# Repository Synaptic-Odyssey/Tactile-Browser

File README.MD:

ABSTRACT:

This project aims to develop a tactile web browsing interface for blind and visually impaired users. Current assistive technology, such as screen readers, forces linear navigation through web pages, preventing users from perceiving spatial layout and efficiently locating interactive elements. The proposed system consists of a 17×11 grid of uniform keycaps (with keyswitches that double as input) that move along the Z-axis using bistable solenoids. Each grouping of blocks represents a distinct webpage element (e.g., headers, links, buttons). When a block is pressed down, the system provides audio feedback, reading the element’s content; prolonged touch can select the element and allow the user to interact with it. By mapping webpage structures into a physical tactile representation, users can explore content spatially and intuitively. Estimated cost for the prototype is ~$800. The project timeline spans two quarters, starting implementing webpage-to-grid mapping, then with the creation of a single 2x5 module, before integrating the entire design.

Detailed Presentation: https://docs.google.com/presentation/d/1p2b0jzcivFLc2I2OcCCj18AWDXcFEL55aIJLbLz9RJQ/edit?slide=id.g39ac1d9ecba_0_35#slide=id.g39ac1d9ecba_0_35

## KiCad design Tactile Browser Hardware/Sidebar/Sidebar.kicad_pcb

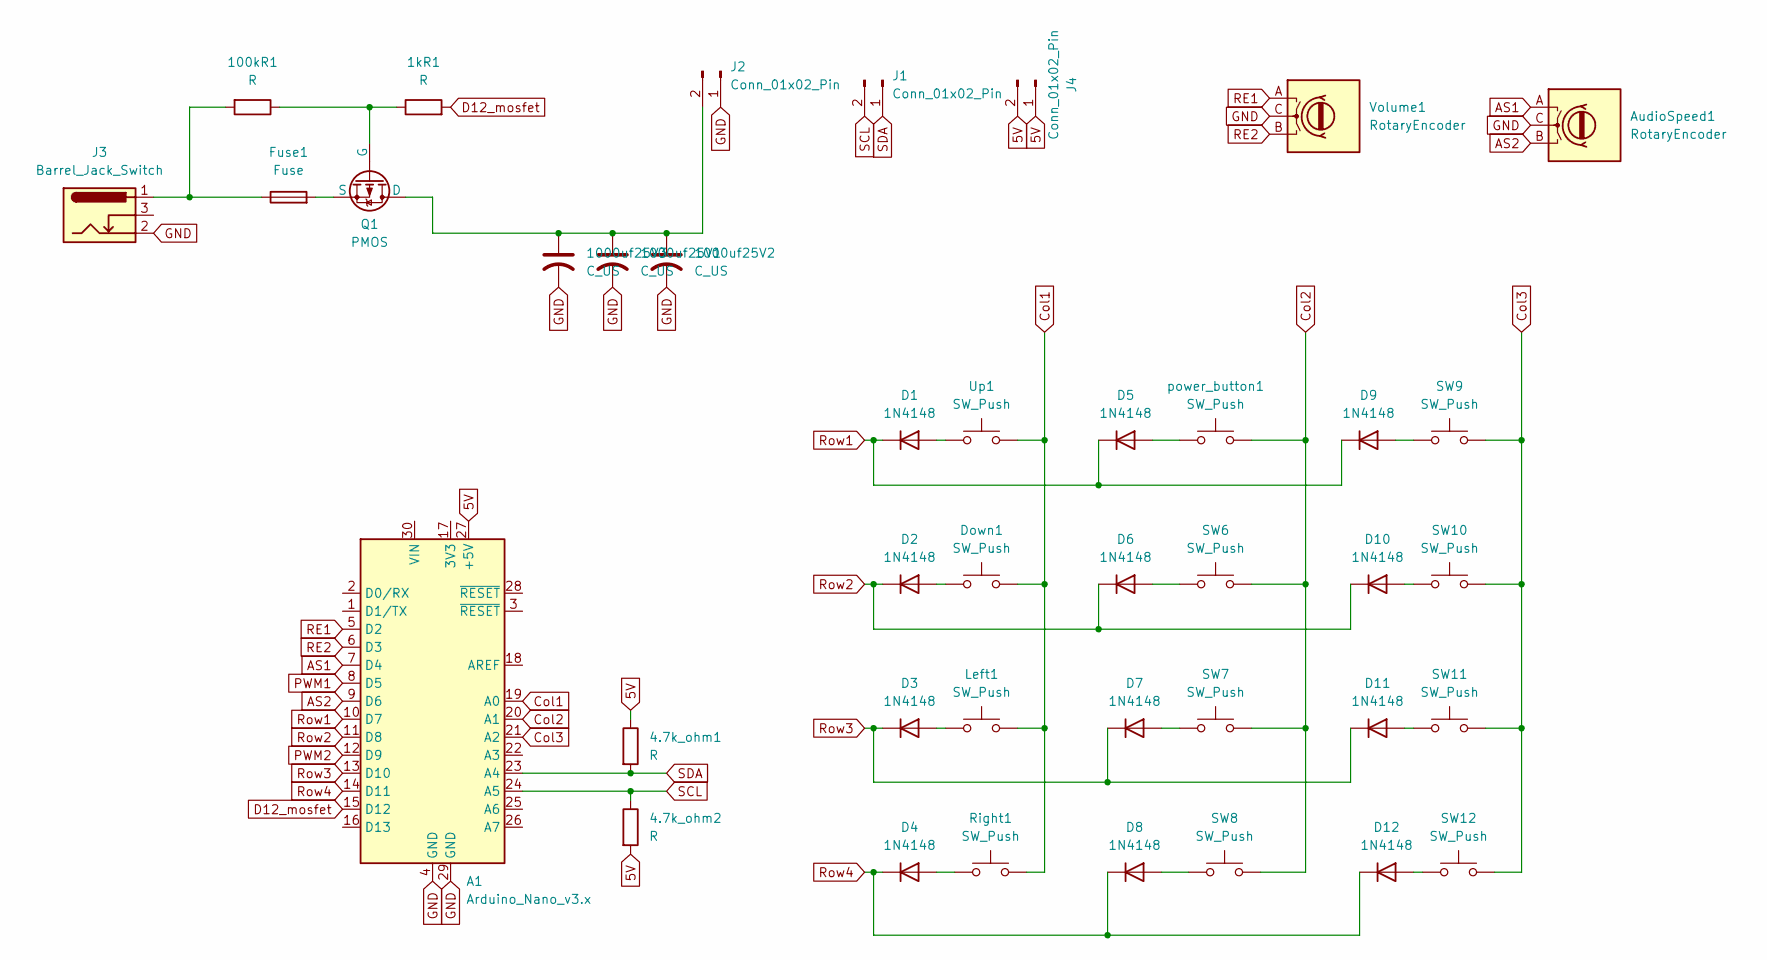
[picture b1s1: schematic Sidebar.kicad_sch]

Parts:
1kR1, 100kR1: R; R_0805_2012Metric
4.7k_ohm1, 4.7k_ohm2: R; R_0402_1005Metric
1000uf25V1, 1000uf25V2, 1000uf25V3: C_US; CP_Elec_10x12.5
A1: Arduino_Nano_v3.x; Arduino_Nano
AudioSpeed1: RotaryEncoder; RotaryEncoder_Alps_EC11E-Switch_Vertical_H20mm
D1, D2, D3, D4, D5, D6, D7, D8, D9, D10, D11, D12: 1N4148; D_SOD-123
Down1: SW_Push; SW_SPST_EVQQ2
Fuse1: Fuse; FUSE_3560
J1, J4: Conn_01x02_Pin; JST_PH_B2B-PH-SM4-TB_1x02-1MP_P2.00mm_Vertical
J2: Conn_01x02_Pin; ScrewTerminal_Vertical_1935310
J3: Barrel_Jack_Switch; BarrelJack_CUI_PJ-063AH_Horizontal
Left1: SW_Push; SW_SPST_EVQQ2
Q1: PMOS; TO-252-3_TabPin2
Right1: SW_Push; SW_SPST_EVQQ2
SW6, SW7, SW8, SW9, SW10, SW11, SW12: SW_Push; SW_SPST_EVQQ2
Up1: SW_Push; SW_SPST_EVQQ2
Volume1: RotaryEncoder; RotaryEncoder_Alps_EC11E-Switch_Vertical_H20mm
power_button1: SW_Push; SW_SPST_EVQQ2

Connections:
5V: 4.7k_ohm1.1, 4.7k_ohm2.2, A1.27 (+5V), J4.1, J4.2
AS1: A1.7 (D4), AudioSpeed1.A
AS2: A1.9 (D6), AudioSpeed1.B
Col1: A1.19 (A0), Down1.2, Left1.2, Right1.2, Up1.2
Col2: A1.20 (A1), SW6.2, SW7.2, SW8.2, power_button1.2
Col3: A1.21 (A2), SW9.2, SW10.2, SW11.2, SW12.2
D12_mosfet: 1kR1.2, A1.15 (D12); also elsewhere on the board
GND: 1000uf25V1.2, 1000uf25V2.2, 1000uf25V3.2, A1.4 (GND), A1.29 (GND), AudioSpeed1.C, J2.1, J3.2, Volume1.C
unnamed 8: 100kR1.2, Fuse1.1, J3.1; also elsewhere on the board
unnamed: D1.2 (A), Up1.1
unnamed: D2.2 (A), Down1.1
unnamed: D3.2 (A), Left1.1
unnamed: D4.2 (A), Right1.1
unnamed: D5.2 (A), power_button1.1
unnamed: D6.2 (A), SW6.1
unnamed: D7.2 (A), SW7.1
unnamed: D8.2 (A), SW8.1
unnamed: D9.2 (A), SW9.1
unnamed: D10.2 (A), SW10.1
unnamed: D11.2 (A), SW11.1
unnamed: D12.2 (A), SW12.1
unnamed: 1000uf25V1.1, 1000uf25V2.1, 1000uf25V3.1, J2.2, Q1.1 (D)
unnamed 22: 1kR1.1, 100kR1.1, Q1.2 (G); also elsewhere on the board
unnamed: Fuse1.2, Q1.3 (S)
PWM1: A1.8 (D5)
PWM2: A1.12 (D9)
RE1: A1.5 (D2), Volume1.A
RE2: A1.6 (D3), Volume1.B
Row1: A1.10 (D7), D1.1 (K), D5.1 (K), D9.1 (K)
Row2: A1.11 (D8), D2.1 (K), D6.1 (K), D10.1 (K)
Row3: A1.13 (D10), D3.1 (K), D7.1 (K), D11.1 (K)
Row4: A1.14 (D11), D4.1 (K), D8.1 (K), D12.1 (K)
SCL: 4.7k_ohm2.1, A1.24 (A5), J1.2
SDA: 4.7k_ohm1.2, A1.23 (A4), J1.1

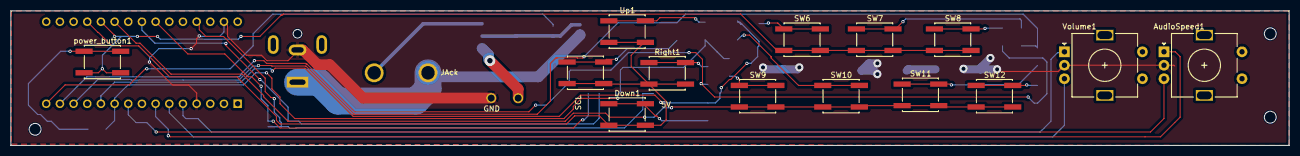
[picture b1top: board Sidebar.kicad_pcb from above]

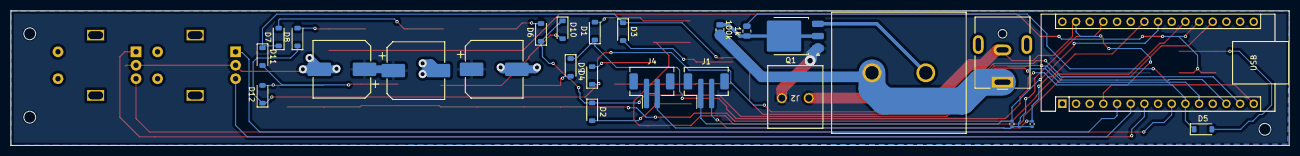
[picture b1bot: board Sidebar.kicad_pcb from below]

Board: 2 copper layers, 237.5 x 25.0 mm, 40 parts (26 on the bottom side), 32 nets.

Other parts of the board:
1k, 100k: R; R_0805_2012Metric

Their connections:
D12_mosfet: 1k.2; also elsewhere on the board
unnamed 8: 100k.2; also elsewhere on the board
unnamed 22: 1k.1, 100k.1; also elsewhere on the board

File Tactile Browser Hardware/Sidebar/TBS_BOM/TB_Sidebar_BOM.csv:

Designator,Comment,Footprint,LCSC Part #
Volume1,RotaryEncoder,RotaryEncoder_Alps_EC11E-Switch_Vertical_H20mm,HAND_SOLDER
AudioSpeed1,RotaryEncoder,RotaryEncoder_Alps_EC11E-Switch_Vertical_H20mm,HAND_SOLDER
power_button1,SW_Push,SW_SPST_EVQQ2,C2976606
Right1,SW_Push,SW_SPST_EVQQ2,C2976606
Down1,SW_Push,SW_SPST_EVQQ2,C2976606
SW10,SW_Push,SW_SPST_EVQQ2,C2976606
Left1,SW_Push,SW_SPST_EVQQ2,C2976606
SW8,SW_Push,SW_SPST_EVQQ2,C2976606
SW6,SW_Push,SW_SPST_EVQQ2,C2976606
Up1,SW_Push,SW_SPST_EVQQ2,C2976606
SW12,SW_Push,SW_SPST_EVQQ2,C2976606
SW11,SW_Push,SW_SPST_EVQQ2,C2976606
SW7,SW_Push,SW_SPST_EVQQ2,C2976606
SW9,SW_Push,SW_SPST_EVQQ2,C2976606
1kR1,R,R_0805_2012Metric,C727989
100kR1,R,R_0805_2012Metric,C161786
A1,Arduino_Nano_v3.x,Arduino_Nano,HAND_SOLDER
1000uf25V2,C_US,CP_Elec_10x12.5,C49256851
1000uf25V3,C_US,CP_Elec_10x12.5,C49256851
1000uf25V1,C_US,CP_Elec_10x12.5,C49256851
D8,1N4148,D_SOD-123,C917030
D9,1N4148,D_SOD-123,C917030
D10,1N4148,D_SOD-123,C917030
D5,1N4148,D_SOD-123,C917030
D6,1N4148,D_SOD-123,C917030
D12,1N4148,D_SOD-123,C917030
D11,1N4148,D_SOD-123,C917030
D3,1N4148,D_SOD-123,C917030
D2,1N4148,D_SOD-123,C917030
D1,1N4148,D_SOD-123,C917030
D4,1N4148,D_SOD-123,C917030
D7,1N4148,D_SOD-123,C917030
Q1,PMOS,TO-252-3_TabPin2,HAND_SOLDER
Fuse1,Fuse,FUSE_3560,HAND_SOLDER
J2,Conn_01x02_Pin,ScrewTerminal_Vertical_1935310,HAND_SOLDER
J4,Conn_01x02_Pin,JST_PH_B2B-PH-SM4-TB_1x02-1MP_P2.00mm_Vertical,C160352
J1,Conn_01x02_Pin,JST_PH_B2B-PH-SM4-TB_1x02-1MP_P2.00mm_Vertical,C160352
4.7k_ohm2,R,R_0402_1005Metric,C105871
4.7k_ohm1,R,R_0402_1005Metric,C105871
J3,Barrel_Jack_Switch,BarrelJack_CUI_PJ-063AH_Horizontal,HAND_SOLDER

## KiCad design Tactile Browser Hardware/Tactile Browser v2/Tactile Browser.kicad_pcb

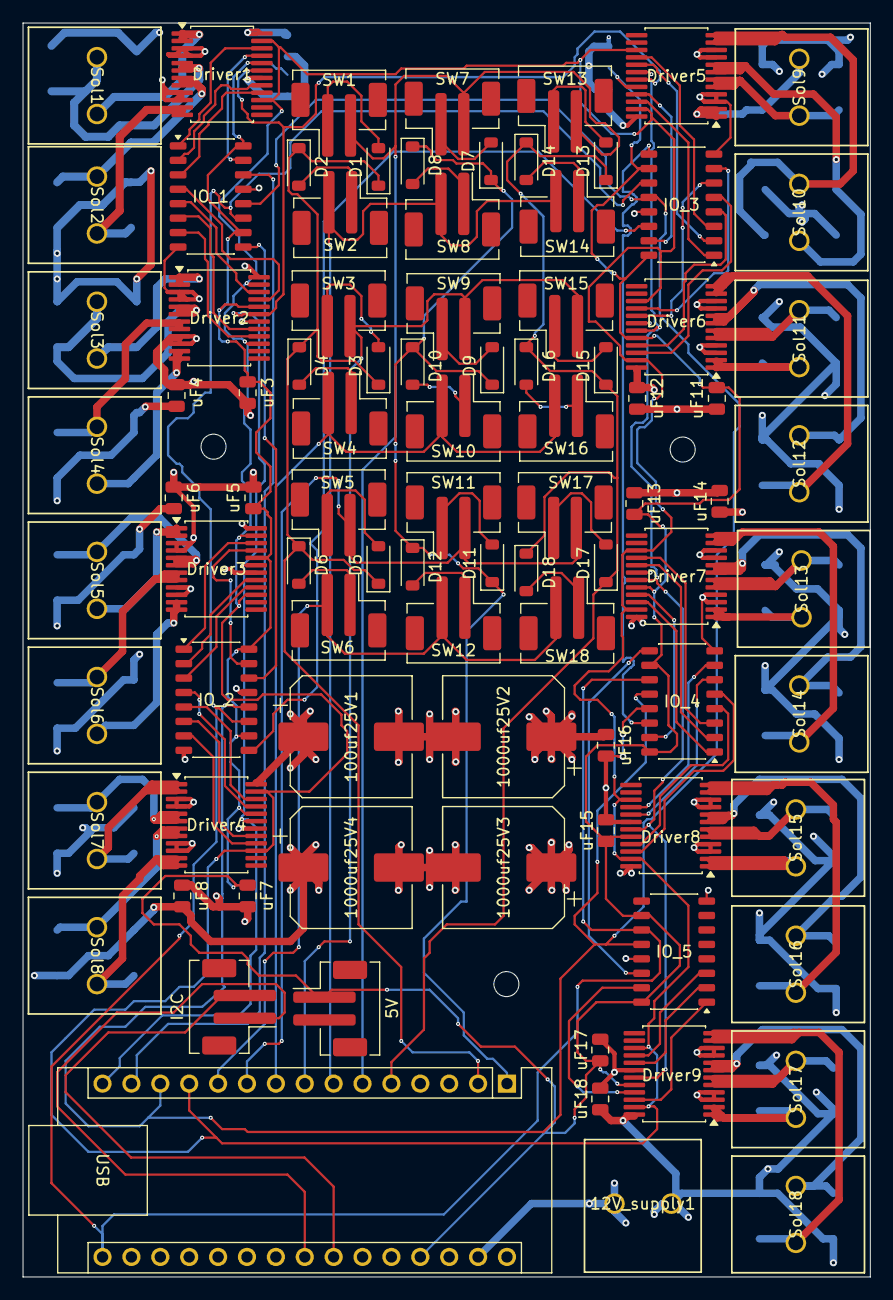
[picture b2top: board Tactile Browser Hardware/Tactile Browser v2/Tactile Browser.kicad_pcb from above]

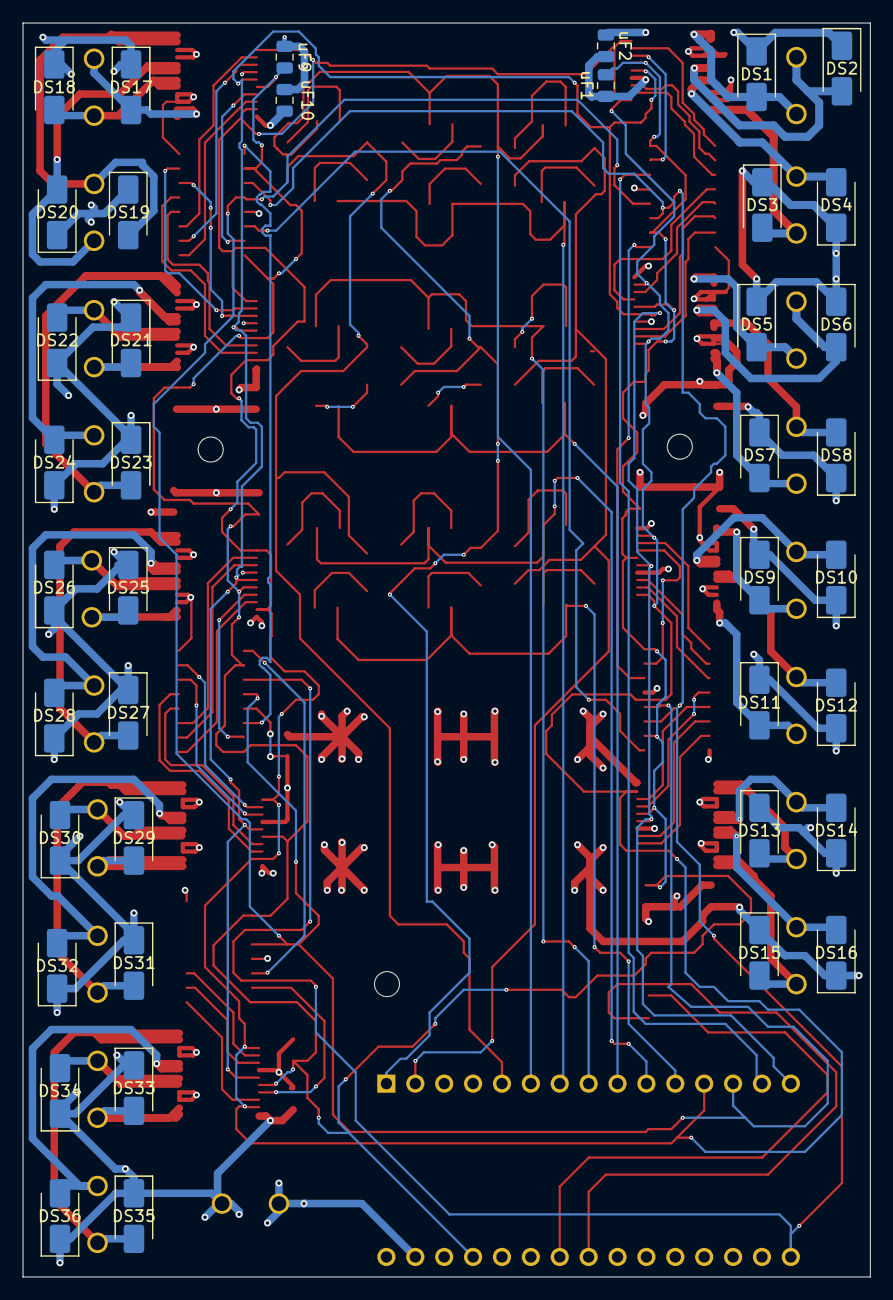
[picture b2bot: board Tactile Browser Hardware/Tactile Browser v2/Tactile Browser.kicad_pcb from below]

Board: 4 copper layers, 74.5 x 110.2 mm, 130 parts (40 on the bottom side), 113 nets.

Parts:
5V: Conn_01x01_Pin; JST_PH_B2B-PH-SM4-TB_1x02-1MP_P2.00mm_Vertical
12V_supply1: Conn_01x02_Pin; ScrewTerminal_Vertical_1935310
100uf25V1, 1000uf25V2, 1000uf25V3, 1000uf25V4: C_Polarized; CP_Elec_10x12.5
A1: Arduino_Nano_v3.x; Arduino_Nano
D1, D2, D3, D4, D5, D6, D7, D8, D9, D10, D11, D12, D13, D14, D15, D16, D17, D18: 1N4148; D_SOD-123
DS1, DS2, DS3, DS4, DS5, DS6, DS7, DS8, DS9, DS10, DS11, DS12, DS13, DS14, DS15, DS16, DS17, DS18, DS19, DS20, DS21, DS22, DS23, DS24, DS25, DS26, DS27, DS28, DS29, DS30, DS31, DS32, DS33, DS34, DS35, DS36: D_Schottky; D_SMA
Driver1, Driver2, Driver3, Driver4, Driver5, Driver6, Driver7, Driver8, Driver9: TB6612FNG; SSOP-24_5.3x8.2mm_P0.65mm
I2C: Conn_01x02_Pin; JST_PH_B2B-PH-SM4-TB_1x02-1MP_P2.00mm_Vertical
IO_1, IO_2, IO_3, IO_4, IO_5: 74HC595; JEITA_SOIC-16_3.9x9.9mm_P1.27mm
SW1, SW2, SW3, SW4, SW5, SW6, SW7, SW8, SW9, SW10, SW11, SW12, SW13, SW14, SW15, SW16, SW17, SW18: SW_Push; JST_PH_B2B-PH-SM4-TB_1x02-1MP_P2.00mm_Vertical
Sol1, Sol2, Sol3, Sol4, Sol5, Sol6, Sol7, Sol8, Sol9, Sol10, Sol11, Sol12, Sol13, Sol14, Sol15, Sol16, Sol17, Sol18: Conn_01x02_Pin; ScrewTerminal_Vertical_1935310
uF1, uF2, uF3, uF4, uF5, uF6, uF7, uF8, uF9, uF10, uF11, uF12, uF13, uF14, uF15, uF16, uF17, uF18: C; C_0805_2012Metric

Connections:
5V: 5V.1, A1.27 (+5V), Driver1.20 (VCC), Driver2.20 (VCC), Driver3.20 (VCC), Driver4.20 (VCC), Driver5.20 (VCC), Driver6.20 (VCC), Driver7.20 (VCC), Driver8.20 (VCC), Driver9.20 (VCC), IO_1.10 (~SRCLR), IO_1.16 (VCC), IO_2.10 (~SRCLR), IO_2.16 (VCC), IO_3.10 (~SRCLR), IO_3.16 (VCC), IO_4.10 (~SRCLR), IO_4.16 (VCC), IO_5.10 (~SRCLR), IO_5.16 (VCC), uF1.2, uF3.2, uF5.2, uF7.1, uF9.1, uF11.1, uF13.1, uF15.1, uF17.1
12V: 12V_supply1.2, 100uf25V1.1, 1000uf25V2.1, 1000uf25V3.1, 1000uf25V4.1, DS1.1 (K), DS2.1 (K), DS3.1 (K), DS4.1 (K), DS5.1 (K), DS6.1 (K), DS7.1 (K), DS8.1 (K), DS9.1 (K), DS10.1 (K), DS11.1 (K), DS12.1 (K), DS13.1 (K), DS14.1 (K), DS15.1 (K), DS16.1 (K), DS17.1 (K), DS18.1 (K), DS19.1 (K), DS20.1 (K), DS21.1 (K), DS22.1 (K), DS23.1 (K), DS24.1 (K), DS25.1 (K), DS26.1 (K), DS27.1 (K), DS28.1 (K), DS29.1 (K), DS30.1 (K), DS31.1 (K), DS32.1 (K), DS33.1 (K), DS34.1 (K), DS35.1 (K), DS36.1 (K), Driver1.24 (VM1), Driver2.24 (VM3), Driver3.24 (VM1), Driver4.24 (VM1), Driver5.24 (VM3), Driver6.24 (VM1), Driver7.24 (VM3), Driver8.24 (VM3), Driver9.24 (VM3), uF2.1, uF4.1, uF6.1, uF8.1, uF10.1, uF12.1, uF14.1, uF16.1, uF18.1
CLOCK: A1.16 (D13), IO_1.11 (SRCLK), IO_2.11 (SRCLK), IO_3.11 (SRCLK), IO_4.11 (SRCLK), IO_5.11 (SRCLK)
Col1: A1.2 (D0/RX), D1.1 (K), D2.1 (K), D3.1 (K), D4.1 (K), D5.1 (K), D6.1 (K)
Col2: A1.1 (D1/TX), D7.1 (K), D8.1 (K), D9.1 (K), D10.1 (K), D11.1 (K), D12.1 (K)
Col3: A1.5 (D2), D13.1 (K), D14.1 (K), D15.1 (K), D16.1 (K), D17.1 (K), D18.1 (K)
DATA: A1.14 (D11), IO_1.14 (SER)
GND: 12V_supply1.1, 100uf25V1.2, 1000uf25V2.2, 1000uf25V3.2, 1000uf25V4.2, A1.4 (GND), A1.29 (GND), Driver1.3 (PGND1), Driver1.4 (PGND1), Driver1.9 (PGND2), Driver1.10 (PGND2), Driver1.18 (GND), Driver2.3 (PGND1), Driver2.4 (PGND1), Driver2.9 (PGND2), Driver2.10 (PGND2), Driver2.18 (GND), Driver3.3 (PGND1), Driver3.4 (PGND1), Driver3.9 (PGND2), Driver3.10 (PGND2), Driver3.18 (GND), Driver4.3 (PGND1), Driver4.4 (PGND1), Driver4.9 (PGND2), Driver4.10 (PGND2), Driver4.18 (GND), Driver5.3 (PGND1), Driver5.4 (PGND1), Driver5.9 (PGND2), Driver5.10 (PGND2), Driver5.18 (GND), Driver6.3 (PGND1), Driver6.4 (PGND1), Driver6.9 (PGND2), Driver6.10 (PGND2), Driver6.18 (GND), Driver7.3 (PGND1), Driver7.4 (PGND1), Driver7.9 (PGND2), Driver7.10 (PGND2), Driver7.18 (GND), Driver8.3 (PGND1), Driver8.4 (PGND1), Driver8.9 (PGND2), Driver8.10 (PGND2), Driver8.18 (GND), Driver9.3 (PGND1), Driver9.4 (PGND1), Driver9.9 (PGND2), Driver9.10 (PGND2), Driver9.18 (GND), IO_1.8 (GND), IO_1.13 (~OE), IO_2.8 (GND), IO_2.13 (~OE), IO_3.8 (GND), IO_3.13 (~OE), IO_4.8 (GND), IO_4.13 (~OE), IO_5.8 (GND), IO_5.13 (~OE), uF1.1, uF2.2, uF3.1, uF4.2, uF5.1, uF6.2, uF7.2, uF8.2, uF9.2, uF10.2, uF11.2, uF12.2, uF13.2, uF14.2, uF15.2, uF16.2, uF17.2, uF18.2
LATCH: A1.13 (D10), IO_1.12 (RCLK), IO_2.12 (RCLK), IO_3.12 (RCLK), IO_4.12 (RCLK), IO_5.12 (RCLK)
unnamed: D1.2 (A), SW1.1
unnamed: D2.2 (A), SW2.1
unnamed: D3.2 (A), SW3.1
unnamed: D4.2 (A), SW4.1
unnamed: D5.2 (A), SW5.1
unnamed: D6.2 (A), SW6.1
unnamed: D7.2 (A), SW7.1
unnamed: D8.2 (A), SW8.1
unnamed: D9.2 (A), SW9.1
unnamed: D10.2 (A), SW10.1
unnamed: D11.2 (A), SW11.1
unnamed: D12.2 (A), SW12.1
unnamed: D13.2 (A), SW13.1
unnamed: D14.2 (A), SW14.1
unnamed: D15.2 (A), SW15.1
unnamed: D16.2 (A), SW16.1
unnamed: D17.2 (A), SW17.1
unnamed: D18.2 (A), SW18.1
Overflow1: IO_1.9 (QH'), IO_2.14 (SER)
Overflow2: IO_2.9 (QH'), IO_3.14 (SER)
Overflow3: IO_3.9 (QH'), IO_4.14 (SER)
Overflow4: IO_4.9 (QH'), IO_5.14 (SER)
PWM: A1.12 (D9), Driver1.15 (PWMB), Driver1.23 (PWMA), Driver2.15 (PWMB), Driver2.23 (PWMA), Driver3.15 (PWMB), Driver3.23 (PWMA), Driver4.15 (PWMB), Driver4.23 (PWMA), Driver5.15 (PWMB), Driver5.23 (PWMA), Driver6.15 (PWMB), Driver6.23 (PWMA), Driver7.15 (PWMB), Driver7.23 (PWMA), Driver8.15 (PWMB), Driver8.23 (PWMA), Driver9.15 (PWMB), Driver9.23 (PWMA)
Row1: A1.6 (D3), SW1.2, SW7.2, SW13.2
Row2: A1.7 (D4), SW2.2, SW8.2, SW14.2
Row3: A1.8 (D5), SW3.2, SW9.2, SW15.2
Row4: A1.9 (D6), SW4.2, SW10.2, SW16.2
Row5: A1.10 (D7), SW5.2, SW11.2, SW17.2
Row6: A1.11 (D8), SW6.2, SW12.2, SW18.2
S1_in1: Driver1.21 (AIN1), IO_1.15 (QA)
S1_in2: Driver1.22 (AIN2), IO_1.1 (QB)
S1_out1: DS1.2 (A), Driver1.1 (AO1), Driver1.2 (AO1), Sol1.2
S1_out2: DS2.2 (A), Driver1.5 (AO2), Driver1.6 (AO2), Sol1.1
S2_in1: Driver1.17 (BIN1), IO_1.2 (QC)
S2_in2: Driver1.16 (BIN2), IO_1.3 (QD)
S2_out1: DS3.2 (A), Driver1.11 (BO1), Driver1.12 (BO1), Sol2.2
S2_out2: DS4.2 (A), Driver1.7 (BO2), Driver1.8 (BO2), Sol2.1
S3_in1: Driver2.21 (AIN1), IO_1.4 (QE)
S3_in2: Driver2.22 (AIN2), IO_1.5 (QF)
S3_out1: DS5.2 (A), Driver2.1 (AO1), Driver2.2 (AO1), Sol3.2
S3_out2: DS6.2 (A), Driver2.5 (AO2), Driver2.6 (AO2), Sol3.1
S4_in1: Driver2.17 (BIN1), IO_1.6 (QG)
S4_in2: Driver2.16 (BIN2), IO_1.7 (QH)
S4_out1: DS7.2 (A), Driver2.11 (BO1), Driver2.12 (BO1), Sol4.2
S4_out2: DS8.2 (A), Driver2.7 (BO2), Driver2.8 (BO2), Sol4.1
S5_in1: Driver3.21 (AIN1), IO_2.15 (QA)
S5_in2: Driver3.22 (AIN2), IO_2.1 (QB)
S5_out1: DS9.2 (A), Driver3.1 (AO1), Driver3.2 (AO1), Sol5.2
S5_out2: DS10.2 (A), Driver3.5 (AO2), Driver3.6 (AO2), Sol5.1
S6_in1: Driver3.17 (BIN1), IO_2.2 (QC)
S6_in2: Driver3.16 (BIN2), IO_2.3 (QD)
S6_out1: DS11.2 (A), Driver3.11 (BO1), Driver3.12 (BO1), Sol6.2
S6_out2: DS12.2 (A), Driver3.7 (BO2), Driver3.8 (BO2), Sol6.1
S7_in1: Driver4.21 (AIN1), IO_2.4 (QE)
S7_in2: Driver4.22 (AIN2), IO_2.5 (QF)
S7_out1: DS13.2 (A), Driver4.1 (AO1), Driver4.2 (AO1), Sol7.2
S7_out2: DS14.2 (A), Driver4.5 (AO2), Driver4.6 (AO2), Sol7.1
S8_in1: Driver4.17 (BIN1), IO_2.6 (QG)
S8_in2: Driver4.16 (BIN2), IO_2.7 (QH)
S8_out1: DS15.2 (A), Driver4.11 (BO1), Driver4.12 (BO1), Sol8.2
S8_out2: DS16.2 (A), Driver4.7 (BO2), Driver4.8 (BO2), Sol8.1
S9_in1: Driver5.21 (AIN1), IO_3.15 (QA)
S9_in2: Driver5.22 (AIN2), IO_3.1 (QB)
S9_out1: DS17.2 (A), Driver5.1 (AO1), Driver5.2 (AO1), Sol9.2
S9_out2: DS18.2 (A), Driver5.5 (AO2), Driver5.6 (AO2), Sol9.1
S10_in1: Driver5.17 (BIN1), IO_3.2 (QC)
S10_in2: Driver5.16 (BIN2), IO_3.3 (QD)
S10_out1: DS19.2 (A), Driver5.11 (BO1), Driver5.12 (BO1), Sol10.2
S10_out2: DS20.2 (A), Driver5.7 (BO2), Driver5.8 (BO2), Sol10.1
S11_in1: Driver6.21 (AIN1), IO_3.4 (QE)
S11_in2: Driver6.22 (AIN2), IO_3.5 (QF)
S11_out1: DS21.2 (A), Driver6.1 (AO1), Driver6.2 (AO1), Sol11.1
S11_out2: DS22.2 (A), Driver6.5 (AO2), Driver6.6 (AO2), Sol11.2
S12_in1: Driver6.17 (BIN1), IO_3.6 (QG)
S12_in2: Driver6.16 (BIN2), IO_3.7 (QH)
S12_out1: DS23.2 (A), Driver6.11 (BO1), Driver6.12 (BO1), Sol12.1
S12_out2: DS24.2 (A), Driver6.7 (BO2), Driver6.8 (BO2), Sol12.2
S13_in1: Driver7.21 (AIN1), IO_4.15 (QA)
S13_in2: Driver7.22 (AIN2), IO_4.1 (QB)
S13_out1: DS25.2 (A), Driver7.1 (AO1), Driver7.2 (AO1), Sol13.1
S13_out2: DS26.2 (A), Driver7.5 (AO2), Driver7.6 (AO2), Sol13.2
S14_in1: Driver7.17 (BIN1), IO_4.2 (QC)
S14_in2: Driver7.16 (BIN2), IO_4.3 (QD)
S14_out1: DS27.2 (A), Driver7.11 (BO1), Driver7.12 (BO1), Sol14.1
S14_out2: DS28.2 (A), Driver7.7 (BO2), Driver7.8 (BO2), Sol14.2
S15_in1: Driver8.21 (AIN1), IO_4.4 (QE)
S15_in2: Driver8.22 (AIN2), IO_4.5 (QF)
S15_out1: DS29.2 (A), Driver8.1 (AO1), Driver8.2 (AO1), Sol15.1
S15_out2: DS30.2 (A), Driver8.5 (AO2), Driver8.6 (AO2), Sol15.2
S16_in1: Driver8.17 (BIN1), IO_4.6 (QG)
S16_in2: Driver8.16 (BIN2), IO_4.7 (QH)
S16_out1: DS31.2 (A), Driver8.11 (BO1), Driver8.12 (BO1), Sol16.1
S16_out2: DS32.2 (A), Driver8.7 (BO2), Driver8.8 (BO2), Sol16.2
S17_in1: Driver9.21 (AIN1), IO_5.15 (QA)
S17_in2: Driver9.22 (AIN2), IO_5.1 (QB)
S17_out1: DS33.2 (A), Driver9.1 (AO1), Driver9.2 (AO1), Sol17.1
S17_out2: DS34.2 (A), Driver9.5 (AO2), Driver9.6 (AO2), Sol17.2
S18_in1: Driver9.17 (BIN1), IO_5.2 (QC)
S18_in2: Driver9.16 (BIN2), IO_5.3 (QD)
S18_out1: DS35.2 (A), Driver9.11 (BO1), Driver9.12 (BO1), Sol18.1
S18_out2: DS36.2 (A), Driver9.7 (BO2), Driver9.8 (BO2), Sol18.2
SCL: A1.24 (A5), I2C.2
SDA: A1.23 (A4), I2C.1
STBY: A1.15 (D12), Driver1.19 (STBY), Driver2.19 (STBY), Driver3.19 (STBY), Driver4.19 (STBY), Driver5.19 (STBY), Driver6.19 (STBY), Driver7.19 (STBY), Driver8.19 (STBY), Driver9.19 (STBY)

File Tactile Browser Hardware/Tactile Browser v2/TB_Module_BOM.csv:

Designator,Value,Footprint,Quantity,LCSC Part #
"SW3,SW4,SW6,SW17,SW8,SW5,SW9,SW12,SW14,SW10,SW15,SW18,SW16,SW2,SW7,SW1,SW13,SW11",SW_Push,JST_PH_B2B-PH-SM4-TB_1x02-1MP_P2.00mm_Vertical,18,C160352
"uF7,uF18,uF8,uF5,uF11,uF16,uF4,uF3,uF12,uF6,uF15,uF14,uF17,uF13,uF2,uF1,uF9,uF10",C,C_0805_2012Metric,18,C141772
"Driver8,Driver5,Driver6,Driver7,Driver2,Driver4,Driver1,Driver9,Driver3",TB6612FNG,SSOP-24_5.3x8.2mm_P0.65mm,9,C141517
"D1,D14,D13,D3,D7,D18,D9,D10,D17,D2,D16,D8,D15,D5,D11,D6,D12,D4",1N4148,D_SOD-123,18,C917030
"1000uf25V2,1000uf25V4,100uf25V1,1000uf25V3",C_Polarized,CP_Elec_10x12.5,4,C49256851
"Sol5,12V_supply1,Sol18,Sol9,Sol17,Sol15,Sol13,Sol14,Sol8,Sol2,Sol7,Sol1,Sol12,Sol3,Sol11,Sol6,Sol16,Sol4,Sol10",Conn_01x02_Pin,ScrewTerminal_Vertical_1935310,19,C6395113
"IO_1,IO_5,IO_4,IO_2,IO_3",74HC595,JEITA_SOIC-16_3.9x9.9mm_P1.27mm,5,C5947
5V,Conn_01x01_Pin,JST_PH_B2B-PH-SM4-TB_1x02-1MP_P2.00mm_Vertical,1,C160352
I2C,Conn_01x02_Pin,JST_PH_B2B-PH-SM4-TB_1x02-1MP_P2.00mm_Vertical,1,C160352
A1,Arduino_Nano_v3.x,Arduino_Nano,1,HAND_SOLDER
"DS22,DS10,DS8,DS27,DS9,DS36,DS26,DS12,DS5,DS15,DS19,DS30,DS7,DS1,DS35,DS24,DS3,DS17,DS6,DS34,DS13,DS28,DS25,DS14,DS31,DS2,DS4,DS18,DS16,DS32,DS29,DS21,DS20,DS33,DS23,DS11",D_Schottky,D_SMA,36,C83852

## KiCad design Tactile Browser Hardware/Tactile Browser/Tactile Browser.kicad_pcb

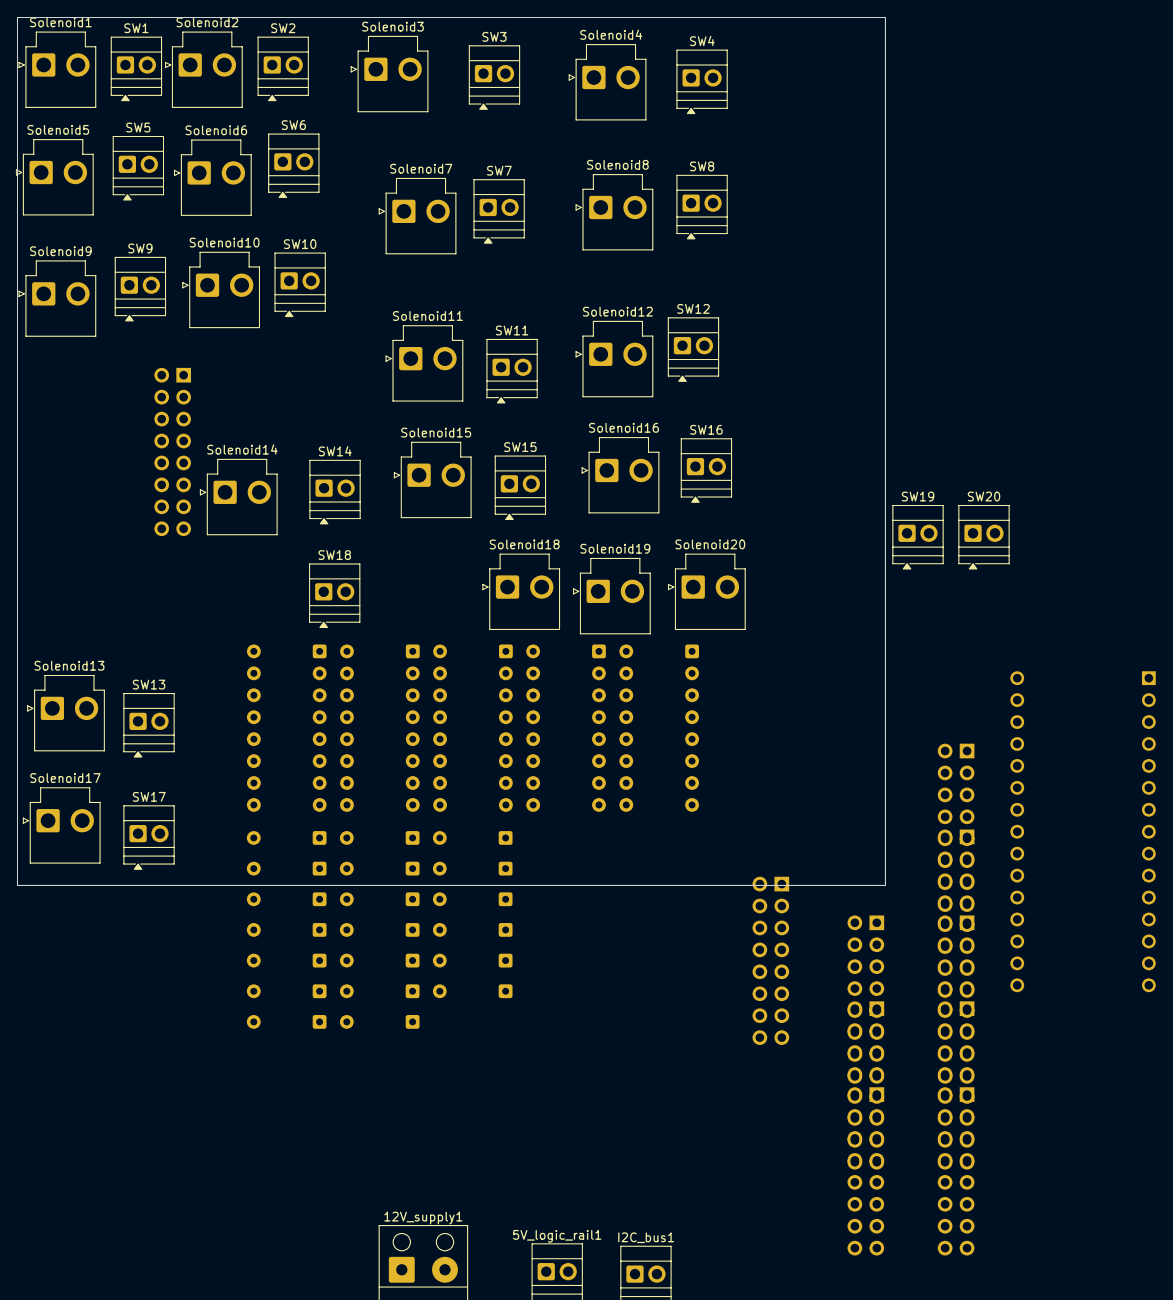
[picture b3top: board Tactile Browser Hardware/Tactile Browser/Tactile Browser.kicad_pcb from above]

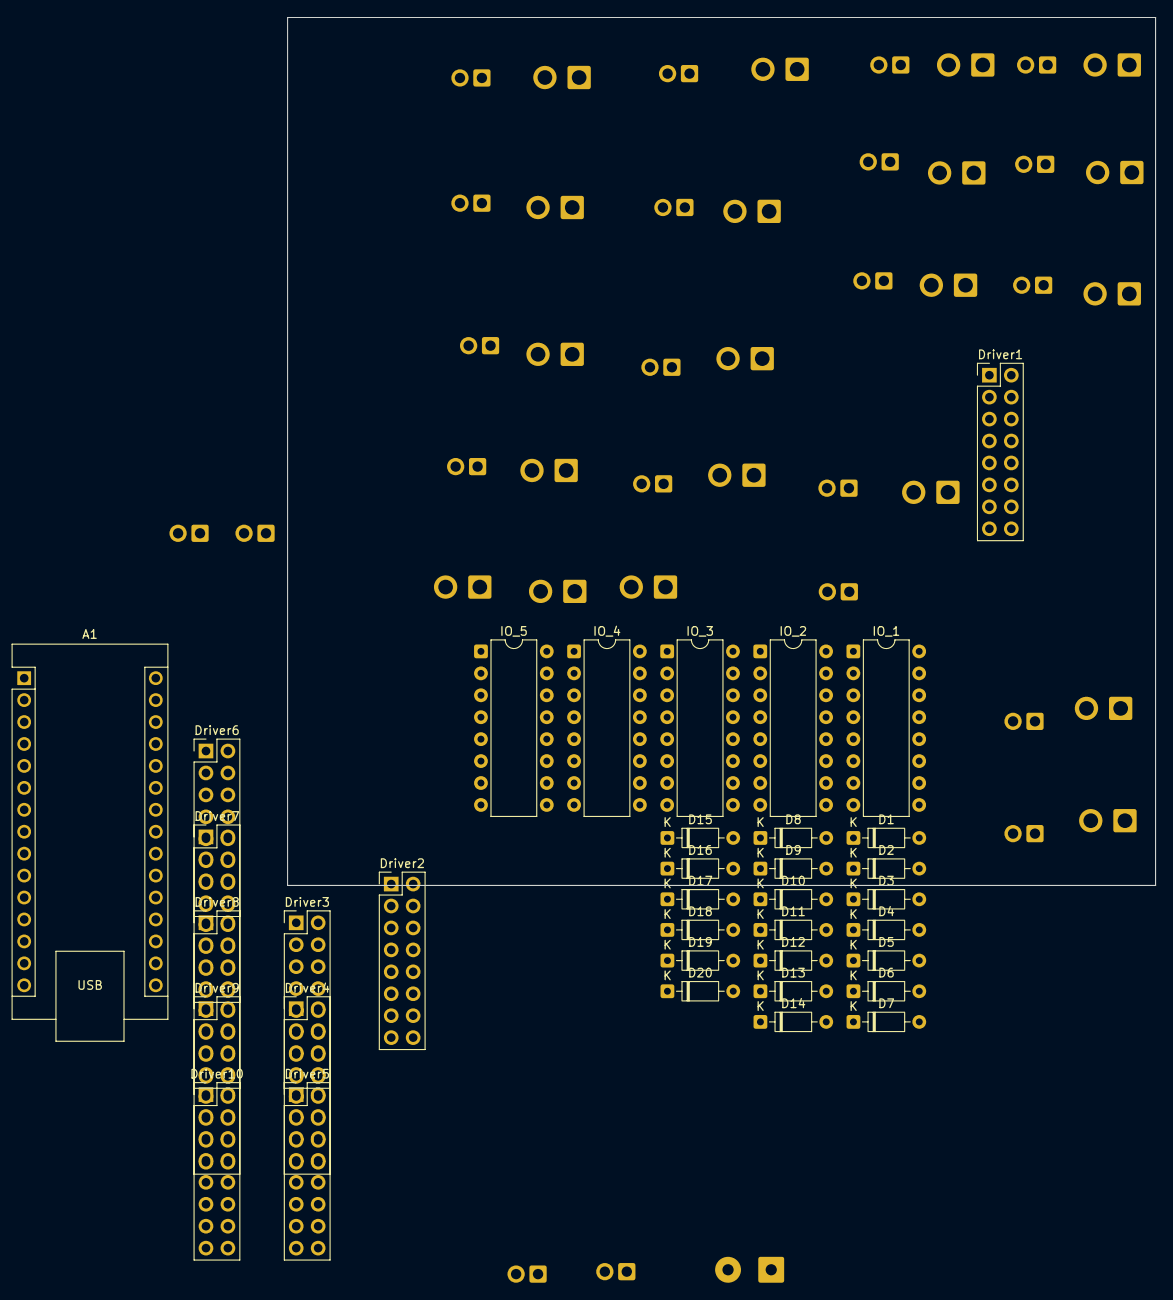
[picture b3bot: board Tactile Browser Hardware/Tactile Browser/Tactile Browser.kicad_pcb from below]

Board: 2 copper layers, 100.5 x 100.5 mm, 79 parts (36 on the bottom side), 92 nets, no tracks yet.

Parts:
5V_logic_rail1: Conn_01x01_Pin; TerminalBlock_Xinya_XY308-2.54-2P_1x02_P2.54mm_Horizontal
12V_supply1: Conn_01x02_Pin; Altech_AK100_1x02_P5.00mm
A1: Arduino_Nano_v3.x; Arduino_Nano
D1, D2, D3, D4, D5, D6, D7, D8, D9, D10, D11, D12, D13, D14, D15, D16, D17, D18, D19, D20: 1N4148; D_DO-35_SOD27_P7.62mm_Horizontal
Driver1, Driver2, Driver3, Driver4, Driver5, Driver6, Driver7, Driver8, Driver9, Driver10: TB6612FNG; PinHeader_2x08_P2.54mm_Vertical
I2C_bus1: Conn_01x02_Pin; TerminalBlock_Xinya_XY308-2.54-2P_1x02_P2.54mm_Horizontal
IO_1, IO_2, IO_3, IO_4, IO_5: 74HC595; DIP-16_W7.62mm
SW1, SW2, SW3, SW4, SW5, SW6, SW7, SW8, SW9, SW10, SW11, SW12, SW13, SW14, SW15, SW16, SW17, SW18, SW19, SW20: SW_Push; TerminalBlock_Xinya_XY308-2.54-2P_1x02_P2.54mm_Horizontal
Solenoid1: Conn_01x02_Pin; JST_VH_B2P-VH_1x02_P3.96mm_Vertical
Solenoid2, Solenoid3, Solenoid4, Solenoid5, Solenoid6, Solenoid7, Solenoid8, Solenoid9, Solenoid10, Solenoid11, Solenoid12, Solenoid13, Solenoid14, Solenoid15, Solenoid16, Solenoid17, Solenoid18, Solenoid19, Solenoid20: Conn_01x02_Pin; JST_VH_B2P-VH-B_1x02_P3.96mm_Vertical

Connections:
5V: 5V_logic_rail1.1, A1.27 (+5V), IO_1.10 (~SRCLR), IO_1.16 (VCC), IO_2.16 (VCC), IO_3.16 (VCC), IO_4.16 (VCC), IO_5.16 (VCC)
12V: 12V_supply1.2, Driver1.13 (VM2), Driver1.14 (VM3), Driver2.13 (VM2), Driver2.14 (VM3), Driver3.13 (VM2), Driver3.14 (VM3), Driver4.13 (VM2), Driver4.14 (VM3), Driver5.13 (VM2), Driver5.14 (VM3), Driver6.13 (VM2), Driver6.14 (VM3), Driver7.13 (VM2), Driver7.14 (VM3), Driver8.13 (VM2), Driver8.14 (VM3), Driver9.13 (VM2), Driver9.14 (VM3), Driver10.13 (VM2), Driver10.14 (VM3)
CLOCK: A1.16 (D13), IO_1.11 (SRCLK), IO_2.11 (SRCLK), IO_3.11 (SRCLK), IO_4.11 (SRCLK), IO_5.11 (SRCLK)
Col1: A1.7 (D4), SW1.2, SW6.2, SW11.2, SW16.2
Col2: A1.8 (D5), SW2.2, SW7.2, SW12.2, SW17.2
Col3: A1.9 (D6), SW3.2, SW8.2, SW13.2, SW18.2
Col4: A1.10 (D7), SW4.2, SW9.2, SW14.2, SW19.2
Col5: A1.11 (D8), SW5.2, SW10.2, SW15.2, SW20.2
DATA: A1.14 (D11), IO_1.14 (SER)
GND: 12V_supply1.1, A1.4 (GND), A1.29 (GND), Driver1.3 (PGND1), Driver1.4 (PGND1), Driver1.9 (PGND2), Driver1.10 (PGND2), Driver2.3 (PGND1), Driver2.4 (PGND1), Driver2.9 (PGND2), Driver2.10 (PGND2), Driver3.3 (PGND1), Driver3.4 (PGND1), Driver3.9 (PGND2), Driver3.10 (PGND2), Driver4.3 (PGND1), Driver4.4 (PGND1), Driver4.9 (PGND2), Driver4.10 (PGND2), Driver5.3 (PGND1), Driver5.4 (PGND1), Driver5.9 (PGND2), Driver5.10 (PGND2), Driver6.3 (PGND1), Driver6.4 (PGND1), Driver6.9 (PGND2), Driver6.10 (PGND2), Driver7.3 (PGND1), Driver7.4 (PGND1), Driver7.9 (PGND2), Driver7.10 (PGND2), Driver8.3 (PGND1), Driver8.4 (PGND1), Driver8.9 (PGND2), Driver8.10 (PGND2), Driver9.3 (PGND1), Driver9.4 (PGND1), Driver9.9 (PGND2), Driver9.10 (PGND2), Driver10.3 (PGND1), Driver10.4 (PGND1), Driver10.9 (PGND2), Driver10.10 (PGND2), IO_1.8 (GND), IO_1.13 (~OE), IO_2.8 (GND), IO_2.13 (~OE), IO_3.8 (GND), IO_3.13 (~OE), IO_4.8 (GND), IO_4.13 (~OE), IO_5.8 (GND), IO_5.13 (~OE)
LATCH: A1.13 (D10), IO_1.12 (RCLK), IO_2.12 (RCLK), IO_3.12 (RCLK), IO_4.12 (RCLK), IO_5.12 (RCLK)
unnamed: D1.2 (A), SW1.1
unnamed: D2.2 (A), SW2.1
unnamed: D3.2 (A), SW3.1
unnamed: D4.2 (A), SW4.1
unnamed: D5.2 (A), SW5.1
unnamed: D6.2 (A), SW6.1
unnamed: D7.2 (A), SW7.1
unnamed: D8.2 (A), SW8.1
unnamed: D9.2 (A), SW9.1
unnamed: D10.2 (A), SW12.1
unnamed: D11.2 (A), SW13.1
unnamed: D12.2 (A), SW14.1
unnamed: D13.2 (A), SW15.1
unnamed: D14.2 (A), SW17.1
unnamed: D15.2 (A), SW18.1
unnamed: D16.2 (A), SW19.1
unnamed: D17.2 (A), SW20.1
unnamed: D18.2 (A), SW11.1
unnamed: D19.2 (A), SW16.1
unnamed: D20.2 (A), SW10.1
Overflow1: IO_1.9 (QH'), IO_2.14 (SER)
Overflow2: IO_2.9 (QH'), IO_3.14 (SER)
Overflow3: IO_3.9 (QH'), IO_4.14 (SER)
Overflow4: IO_4.9 (QH'), IO_5.14 (SER)
PWM: A1.12 (D9), Driver1.15 (PWMB), Driver2.15 (PWMB), Driver3.15 (PWMB), Driver4.15 (PWMB), Driver5.15 (PWMB), Driver6.15 (PWMB), Driver7.15 (PWMB), Driver8.15 (PWMB), Driver9.15 (PWMB), Driver10.15 (PWMB)
Row1: A1.2 (D0/RX), D1.1 (K), D2.1 (K), D3.1 (K), D4.1 (K), D5.1 (K)
Row2: A1.1 (D1/TX), D6.1 (K), D7.1 (K), D8.1 (K), D9.1 (K), D20.1 (K)
Row3: A1.5 (D2), D10.1 (K), D11.1 (K), D12.1 (K), D13.1 (K), D18.1 (K)
Row4: A1.6 (D3), D14.1 (K), D15.1 (K), D16.1 (K), D17.1 (K), D19.1 (K)
S1_out1: Driver1.1 (AO1), Driver1.2 (AO1), Solenoid1.2
S1_out2: Driver1.5 (AO2), Driver1.6 (AO2), Solenoid1.1
S2_in2: Driver1.16 (BIN2), IO_1.3 (QD)
S2_out1: Driver1.11 (BO1), Driver1.12 (BO1), Solenoid2.2
S2_out2: Driver1.7 (BO2), Driver1.8 (BO2), Solenoid2.1
S3_out1: Driver2.1 (AO1), Driver2.2 (AO1), Solenoid3.2
S3_out2: Driver2.5 (AO2), Driver2.6 (AO2), Solenoid3.1
S4_in2: Driver2.16 (BIN2), IO_1.7 (QH)
S4_out1: Driver2.11 (BO1), Driver2.12 (BO1), Solenoid4.2
S4_out2: Driver2.7 (BO2), Driver2.8 (BO2), Solenoid4.1
S5_out1: Driver3.1 (AO1), Driver3.2 (AO1), Solenoid5.2
S5_out2: Driver3.5 (AO2), Driver3.6 (AO2), Solenoid5.1
S6_in2: Driver3.16 (BIN2), IO_2.3 (QD)
S6_out1: Driver3.11 (BO1), Driver3.12 (BO1), Solenoid6.2
S6_out2: Driver3.7 (BO2), Driver3.8 (BO2), Solenoid6.1
S7_out1: Driver4.1 (AO1), Driver4.2 (AO1), Solenoid7.2
S7_out2: Driver4.5 (AO2), Driver4.6 (AO2), Solenoid7.1
S8_in2: Driver4.16 (BIN2), IO_2.7 (QH)
S8_out1: Driver4.11 (BO1), Driver4.12 (BO1), Solenoid8.2
S8_out2: Driver4.7 (BO2), Driver4.8 (BO2), Solenoid8.1
S9_out1: Driver5.1 (AO1), Driver5.2 (AO1), Solenoid9.2
S9_out2: Driver5.5 (AO2), Driver5.6 (AO2), Solenoid9.1
S10_in2: Driver5.16 (BIN2), IO_3.3 (QD)
S10_out1: Driver5.11 (BO1), Driver5.12 (BO1), Solenoid10.2
S10_out2: Driver5.7 (BO2), Driver5.8 (BO2), Solenoid10.1
S11_out1: Driver6.1 (AO1), Driver6.2 (AO1), Solenoid20.1
S11_out2: Driver6.5 (AO2), Driver6.6 (AO2), Solenoid20.2
S12_in2: Driver6.16 (BIN2), IO_3.7 (QH)
S12_out1: Driver6.11 (BO1), Driver6.12 (BO1), Solenoid19.1
S12_out2: Driver6.7 (BO2), Driver6.8 (BO2), Solenoid19.2
S13_out1: Driver7.1 (AO1), Driver7.2 (AO1), Solenoid18.1
S13_out2: Driver7.5 (AO2), Driver7.6 (AO2), Solenoid18.2
S14_in2: Driver7.16 (BIN2), IO_4.3 (QD)
S14_out1: Driver7.11 (BO1), Driver7.12 (BO1), Solenoid17.1
S14_out2: Driver7.7 (BO2), Driver7.8 (BO2), Solenoid17.2
S15_out1: Driver8.1 (AO1), Driver8.2 (AO1), Solenoid15.1
S15_out2: Driver8.5 (AO2), Driver8.6 (AO2), Solenoid15.2
S16_in2: Driver8.16 (BIN2), IO_4.7 (QH)
S16_out1: Driver8.11 (BO1), Driver8.12 (BO1), Solenoid16.1
S16_out2: Driver8.7 (BO2), Driver8.8 (BO2), Solenoid16.2
S17_out1: Driver9.1 (AO1), Driver9.2 (AO1), Solenoid14.1
S17_out2: Driver9.5 (AO2), Driver9.6 (AO2), Solenoid14.2
S18_in2: Driver9.16 (BIN2), IO_5.3 (QD)
S18_out1: Driver9.11 (BO1), Driver9.12 (BO1), Solenoid13.1
S18_out2: Driver9.7 (BO2), Driver9.8 (BO2), Solenoid13.2
S19_out1: Driver10.1 (AO1), Driver10.2 (AO1), Solenoid11.1
S19_out2: Driver10.5 (AO2), Driver10.6 (AO2), Solenoid11.2
S20_in2: Driver10.16 (BIN2), IO_5.7 (QH)
S20_out1: Driver10.11 (BO1), Driver10.12 (BO1), Solenoid12.1
S20_out2: Driver10.7 (BO2), Driver10.8 (BO2), Solenoid12.2
SCL: A1.24 (A5), I2C_bus1.2
SDA: A1.23 (A4), I2C_bus1.1

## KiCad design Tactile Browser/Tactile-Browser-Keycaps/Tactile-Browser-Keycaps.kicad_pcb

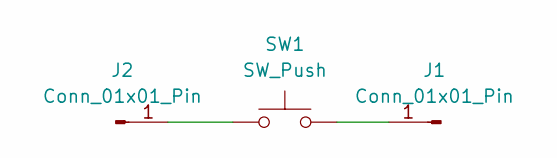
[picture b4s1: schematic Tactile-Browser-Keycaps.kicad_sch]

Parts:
J1, J2: Conn_01x01_Pin; PinHeader_1x01_P2.54mm_Horizontal
SW1: SW_Push; SW_Cherry_MX_1.00u_PCB

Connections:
unnamed: J1.1, SW1.2
unnamed: J2.1, SW1.1

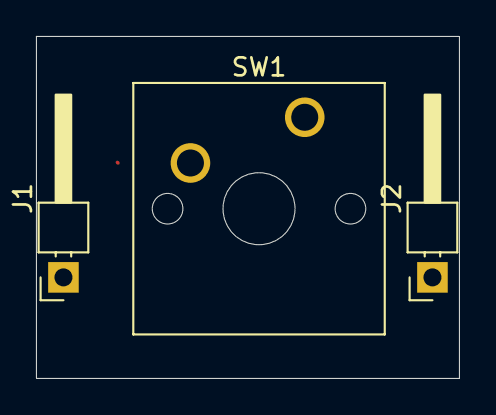
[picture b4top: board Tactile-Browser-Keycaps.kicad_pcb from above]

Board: 2 copper layers, 23.5 x 19.0 mm, 3 parts (0 on the bottom side), 2 nets.

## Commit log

2025-10-14 initial + abstract
2025-10-29 basic layout
2025-10-29 html element class completed
2025-10-30 updated tactile patterns
2025-10-30 ready for testing
2025-10-30 test 1
2025-11-01 fixed
2025-11-03 Big mistake
    Instead of just parsing the HTML files, need to actually parse the rendered DOM. Thus it becomes a chrome extension
2025-11-03 new file structure
    For chrome extension + native app
2025-11-04 content
2025-11-04 ready to test
2025-11-05 native messaging
2025-11-05 testing native messaging
2025-11-05 testing success
2025-11-27 finished schematic for each module!!
2025-11-27 Kicad
2025-11-28 more sidebar progress
2025-12-19 sidebar progress
2025-12-20 electrical safety
2025-12-24 set up platform.io
2025-12-24 this time actually added platform.io
2026-01-05 test code
2026-01-05 moved all solenoids to 74hc595s
2026-01-06 added footprints to module
2026-01-06 pcb edits + updated driver footprint
2026-01-06 pcb edits
2026-01-07 board testing
2026-01-19 2nd module iteration
    downsizing, dedicated SPI connectors, rearrangeable products
2026-01-19 updated module schematic
2026-02-06 updated solenoid/keyswitch connectors
    for ease of manufacturing
2026-02-06 pcb design
2026-02-06 actually fit everything onto the board I'm a genuis
2026-02-06 made pcb even smaller
2026-02-07 Fixed huge solenoid netting issue
2026-02-07 a ton of work on the pcb
2026-02-09 integrated drivers
    added schottky diodes, bulk & decoupling capacitors
2026-02-09 updated pcb
2026-02-13 updated capacitors
2026-02-14 changed to vertical screw terminals
2026-02-14 solenoid wiring!!
2026-02-14 made the board even smaller!
2026-02-14 capacitor naming scheme
2026-02-15 schottky diode placement
2026-02-15 more work on pcb
2026-02-15 PCB almost done!
2026-02-16 code for single solenoid
2026-02-16 more pcb work
2026-02-16 almost done with pcb!
2026-02-16 ground +12V planes
2026-02-19 ran drc, finished routing
2026-03-02 FINISHED PCB
    resolved DRC, added drill holes,
2026-03-02 prepped pcb for assembly
2026-03-02 S_out vias
2026-03-08 stuff
2026-03-23 sidebar updates
2026-03-23 finished with sidebar schematic!
2026-03-24 finished footprints (mostly)
2026-03-24 started sidebar pcb
2026-03-24 finished pcb placement
2026-03-25 added power mosfet
2026-03-25 correct mosfet footprints
2026-03-25 finally got the right fuse
2026-03-25 footprint placement
2026-03-25 sidebar pcb progress
2026-03-25 done with pcb connections
2026-03-25 finished filled zones! (sidebar)
2026-03-25 FINISHED SIDEBAR!!!
2026-03-25 FINISHED SIDEBAR
2026-03-25 added m2 screws
2026-03-26 ketyswitch
2026-03-26 finished keyswitch
2026-03-26 save
2026-03-26 prep for manufacturing
2026-03-28 manufacturing
2026-04-15 ieee mwscas paper
2026-05-27 Module prototype
    I still need to upload the 3d files for the casings I made, but the main thing is over the past few months I've ordered and soldered all the pcbs and they are all working!! I should've uploaded more 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
2026-05-28 module works!
2026-05-28 working better
    but no audio still
2026-06-21 udpated code
